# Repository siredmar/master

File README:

02.03.2014 - This is the repository for my masters thesis

-- Armin Schlegel

GIT instructions:
* adding new files
git add *

* deleting files from repo
git rm *

* commit changed files:
git commit -am 'message'

* push commit to github
git push origin master

* update local repo from github
git pull

--- 
creating a patch:
diff -uNr  original/ new/ > original.patch

use a patch:
cd original
patch -p1 < ../patch.file

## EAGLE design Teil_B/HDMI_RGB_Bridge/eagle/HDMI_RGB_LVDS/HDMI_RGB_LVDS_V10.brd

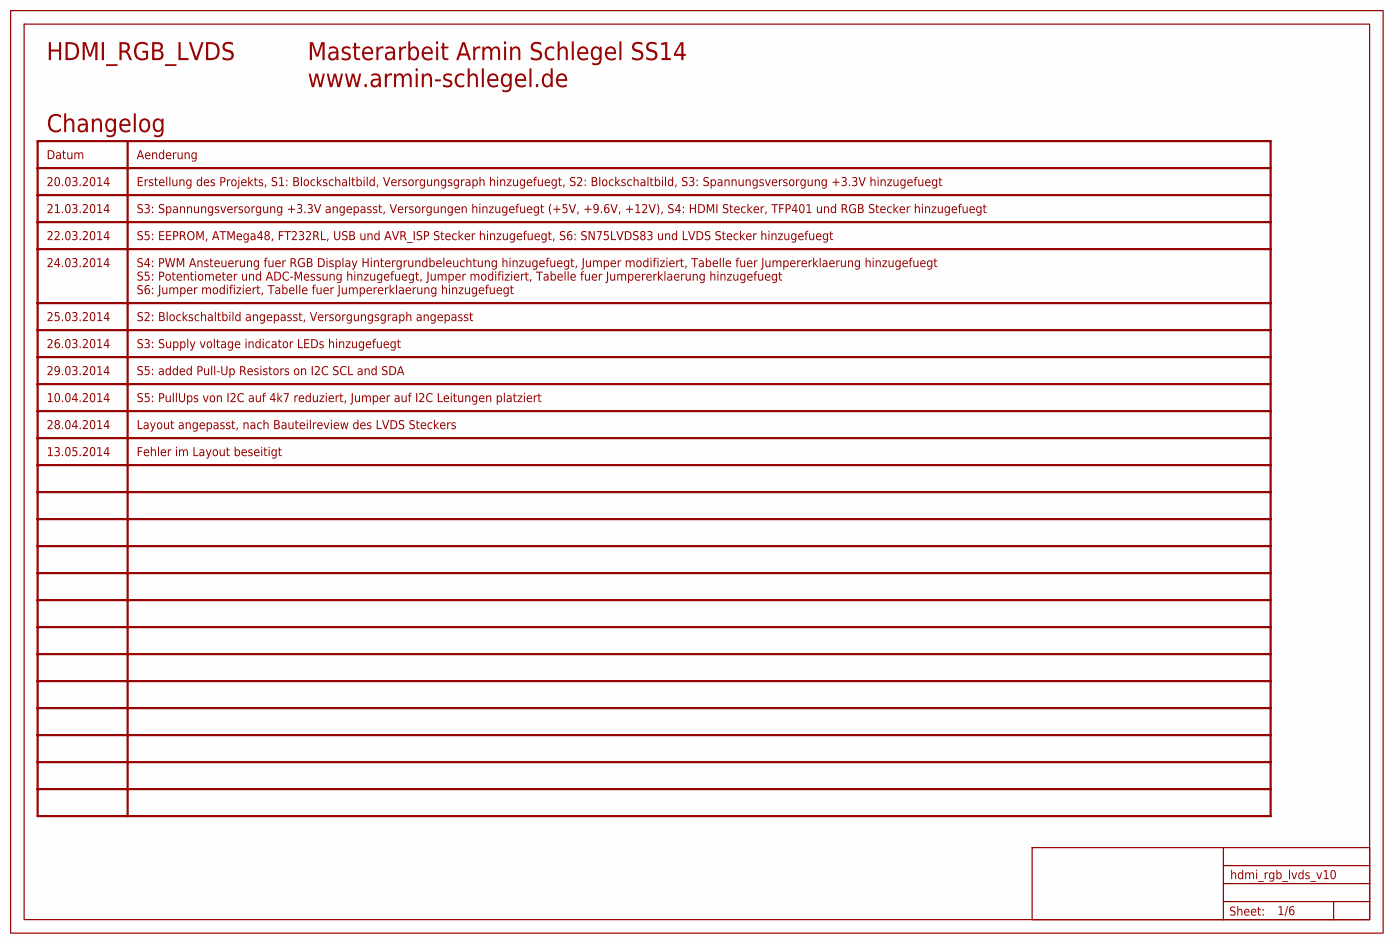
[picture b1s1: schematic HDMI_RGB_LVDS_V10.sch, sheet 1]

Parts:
U$1: FRAME_A3_LANDSCAPE; FRAME

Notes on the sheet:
Erstellung des Projekts, S1: Blockschaltbild, Versorgungsgraph hinzugefuegt, S2: Blockschaltbild, S3: Spannungsversorgung +3.3V hinzugefuegt
HDMI_RGB_LVDS
Masterarbeit Armin Schlegel SS14
www.armin-schlegel.de
Changelog
20.03.2014
Datum
Aenderung
21.03.2014
S3: Spannungsversorgung +3.3V angepasst, Versorgungen hinzugefuegt (+5V, +9.6V, +12V), S4: HDMI Stecker, TFP401 und RGB Stecker hinzugefuegt
22.03.2014
S5: EEPROM, ATMega48, FT232RL, USB und AVR_ISP Stecker hinzugefuegt, S6: SN75LVDS83 und LVDS Stecker hinzugefuegt
24.03.2014
S4: PWM Ansteuerung fuer RGB Display Hintergrundbeleuchtung hinzugefuegt, Jumper modifiziert, Tabelle fuer Jumpererklaerung hinzugefuegt S5: Potentiometer und ADC-Messung hinzugefuegt, Jumper modifiziert, Tabelle fuer Jumpererklaerung hinzugefuegt S6: Jumper modifiziert, Tabelle fuer Jumpererklaeru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
25.03.2014
S2: Blockschaltbild angepasst, Versorgungsgraph angepasst
26.03.2014
S3: Supply voltage indicator LEDs hinzugefuegt
29.03.2014
S5: added Pull-Up Resistors on I2C SCL and SDA
10.04.2014
S5: PullUps von I2C auf 4k7 reduziert, Jumper auf I2C Leitungen platziert
28.04.2014
Layout angepasst, nach Bauteilreview des LVDS Steckers
13.05.2014
Fehler im Layout beseitigt

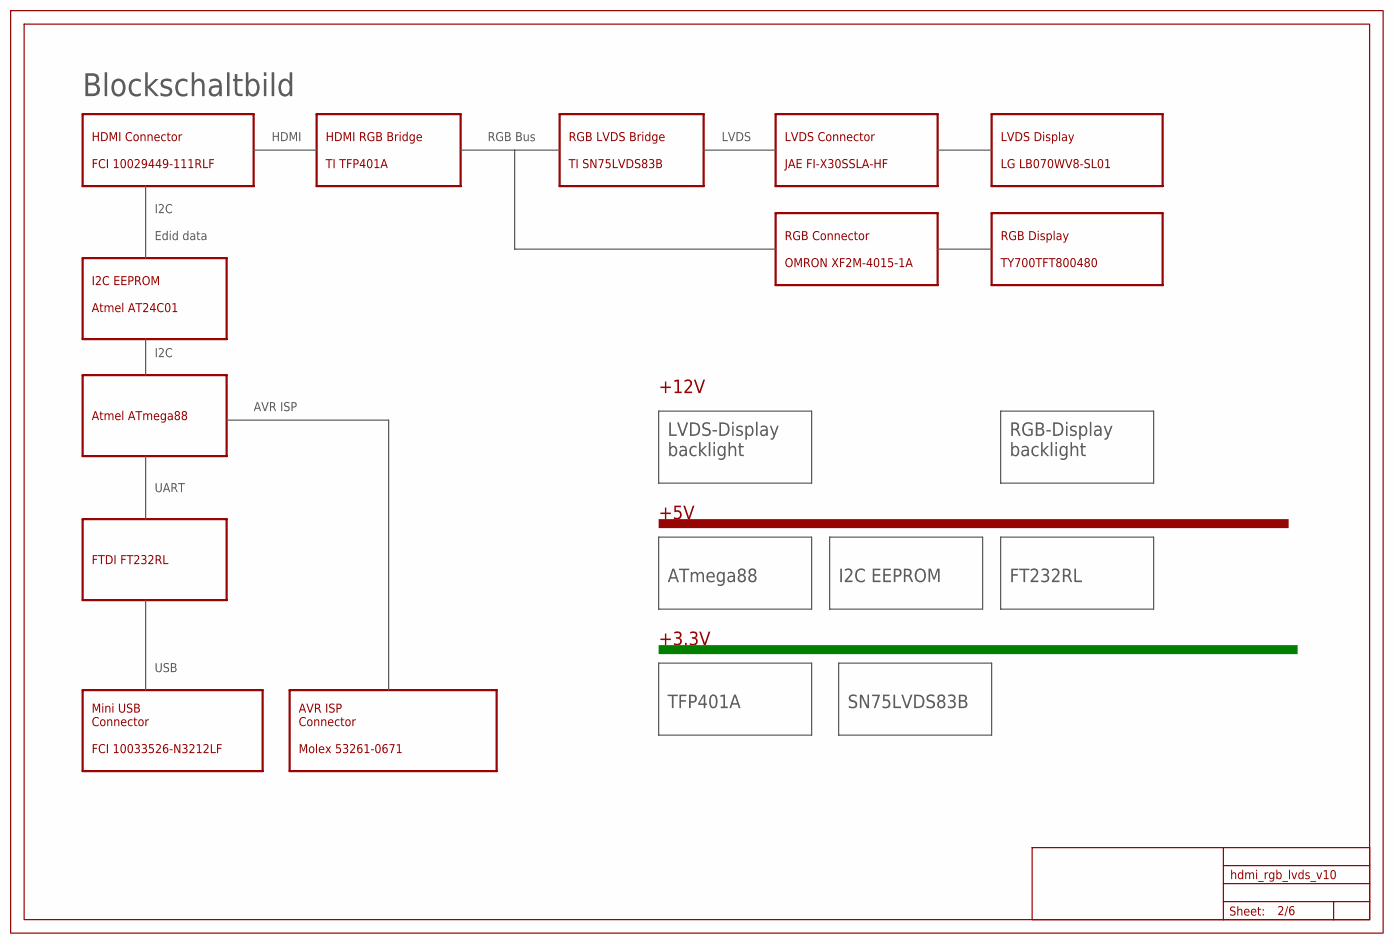
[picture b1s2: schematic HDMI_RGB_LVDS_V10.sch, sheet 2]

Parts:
U$15: FRAME_A3_LANDSCAPE; FRAME

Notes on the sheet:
HDMI Connector FCI 10029449-111RLF
LVDS Display LG LB070WV8-SL01
RGB Display TY700TFT800480
Mini USB Connector FCI 10033526-N3212LF
AVR ISP Connector Molex 53261-0671
LVDS Connector JAE FI-X30SSLA-HF
RGB Connector OMRON XF2M-4015-1A
HDMI RGB Bridge TI TFP401A
RGB LVDS Bridge TI SN75LVDS83B
I2C EEPROM Atmel AT24C01
Atmel ATmega88
Edid data
RGB Bus
LVDS
I2C
USB
AVR ISP
HDMI
Blockschaltbild
+3.3V
+12V
+5V
ATmega88
I2C EEPROM
FT232RL
TFP401A
LVDS-Display backlight
FTDI FT232RL
UART
RGB-Display backlight
SN75LVDS83B

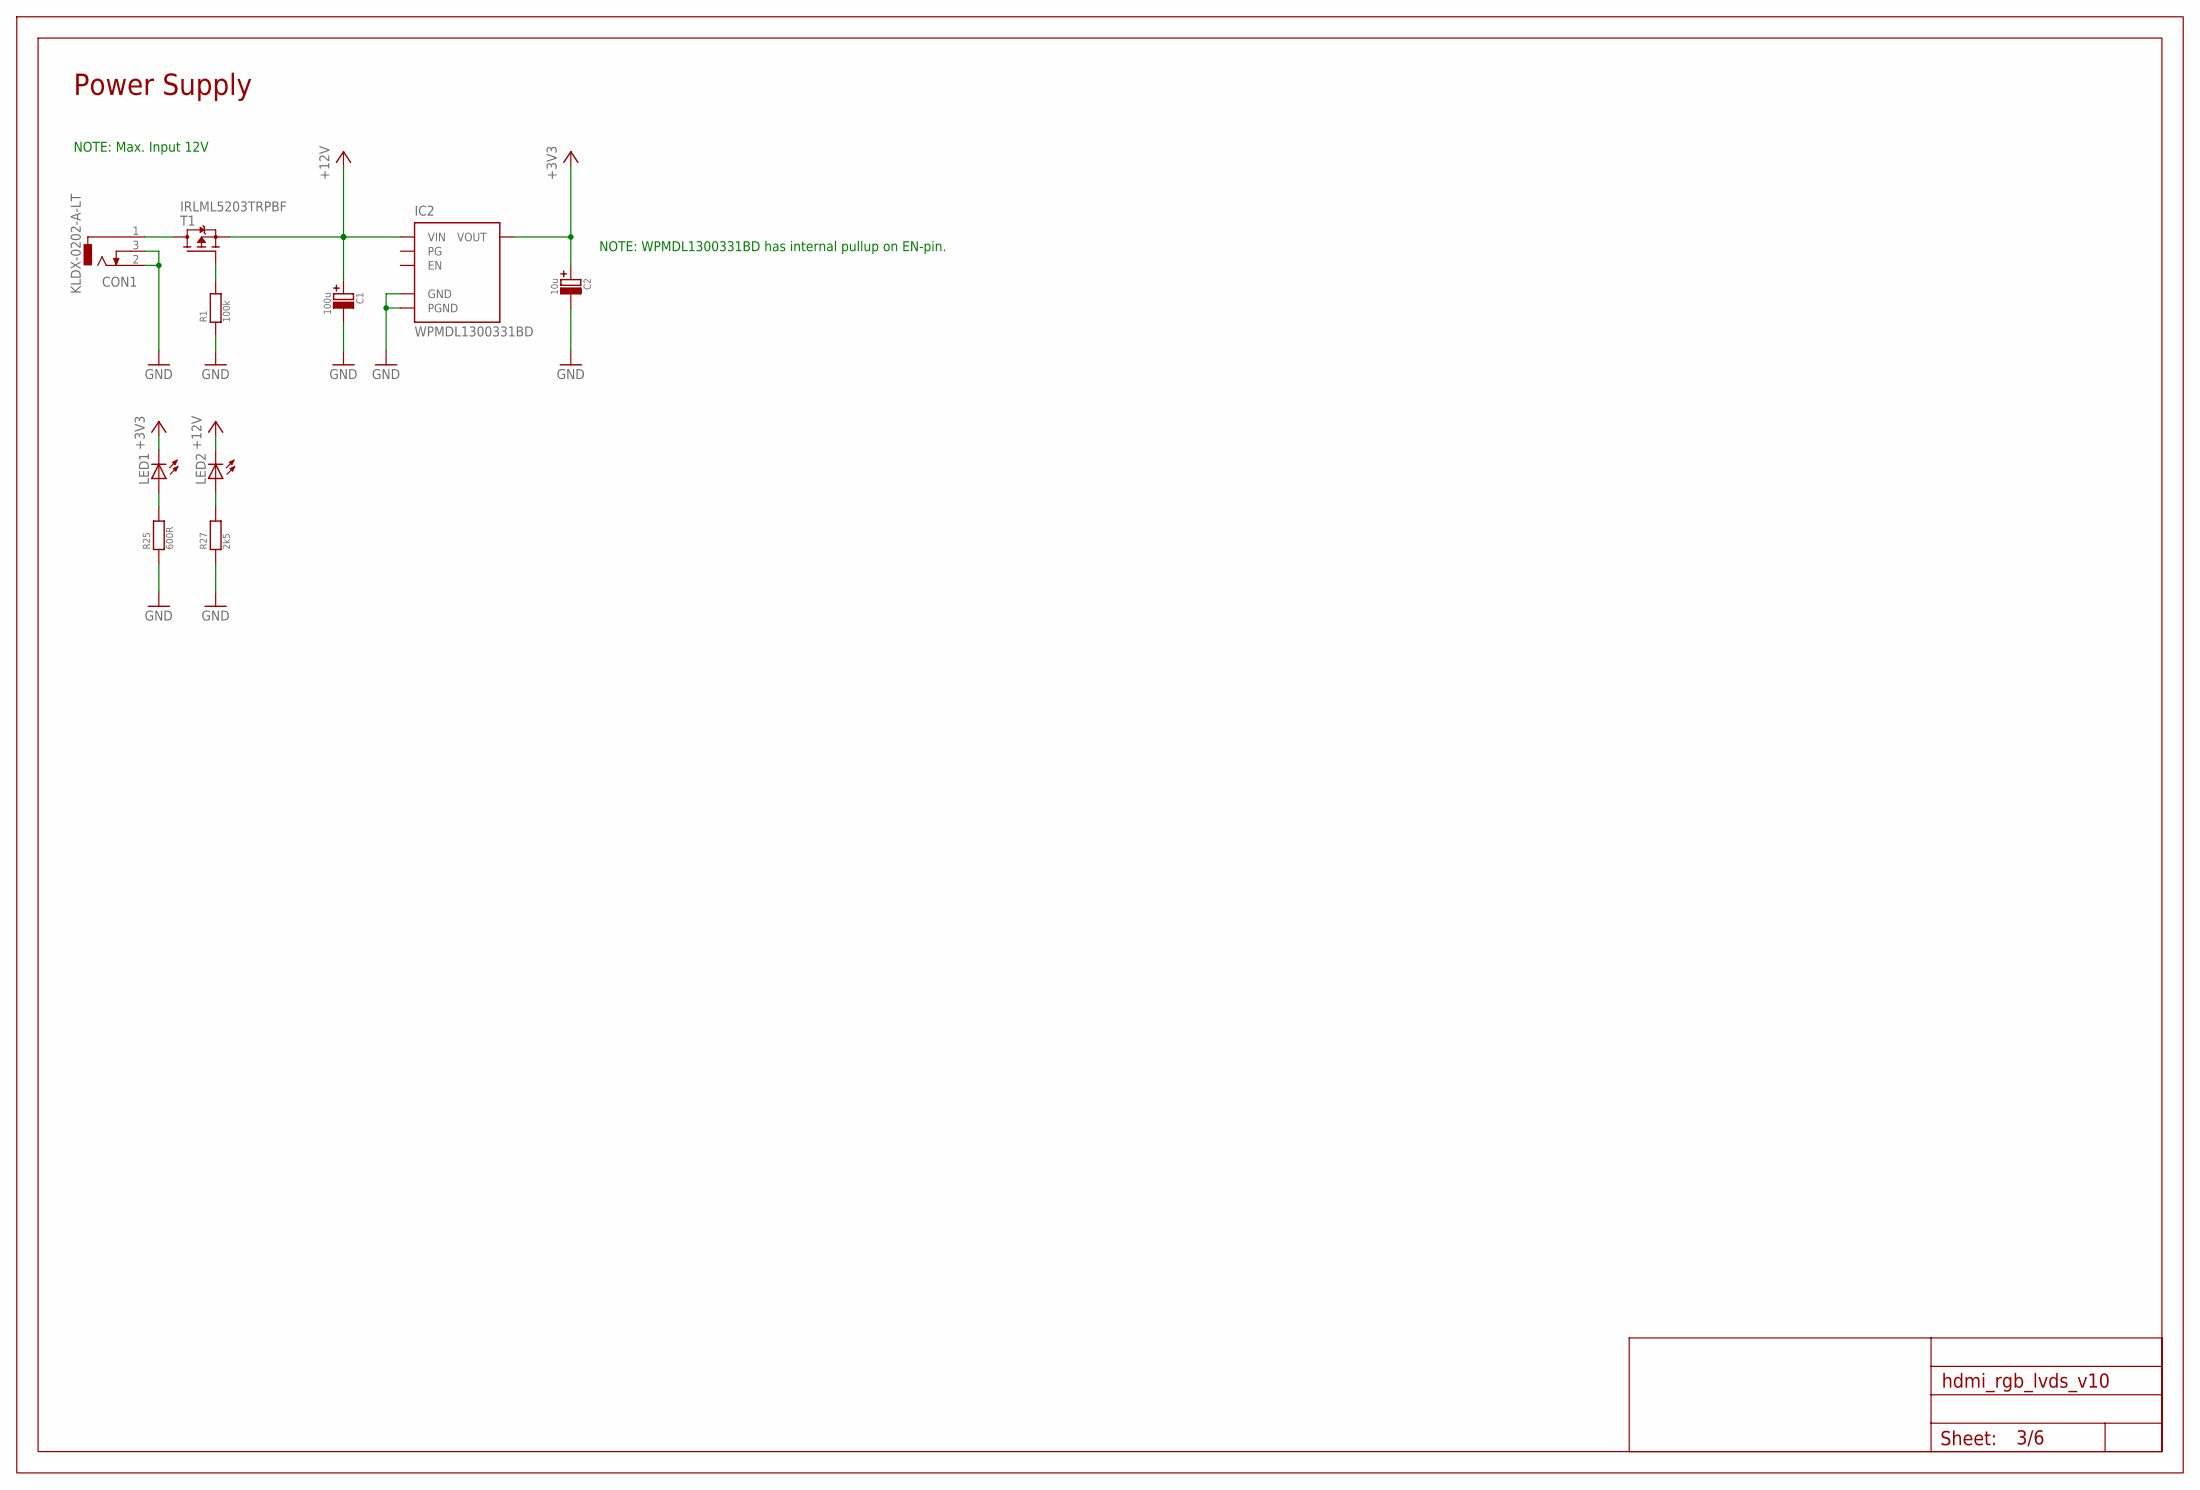
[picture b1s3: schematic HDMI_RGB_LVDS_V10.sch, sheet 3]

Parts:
C1: 100u; C_POL_6X6MM
C2: 10u; C_POL_4X4MM
CON1: KLDX-0202-A-LT
IC2: WPMDL1300331BD; TO263-5
LED1, LED2: LED0402
R1: 100k; R0402
R25: 600R; R0402
R27: 2k5; R0402
T1: IRLML5203TRPBF; SOT23
U$2: FRAME_A3_LANDSCAPE; FRAME

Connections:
+3V3: C2.+, IC2.3 (VOUT), LED1.C; also elsewhere on the board
+12V: C1.+, IC2.1 (VIN), LED2.C, T1.2 (S); also elsewhere on the board
GND: C1.-, C2.-, CON1.2 (3), CON1.3 (2), IC2.2 (GND), IC2.6 (PGND), R1.1, R25.1, R27.1; also elsewhere on the board
unnamed: CON1.1, T1.3 (D)
unnamed: R1.2, T1.1 (G)
unnamed: LED1.A, R25.2
unnamed: LED2.A, R27.2

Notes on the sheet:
Power Supply
NOTE: WPMDL1300331BD has internal pullup on EN-pin.
NOTE: Max. Input 12V

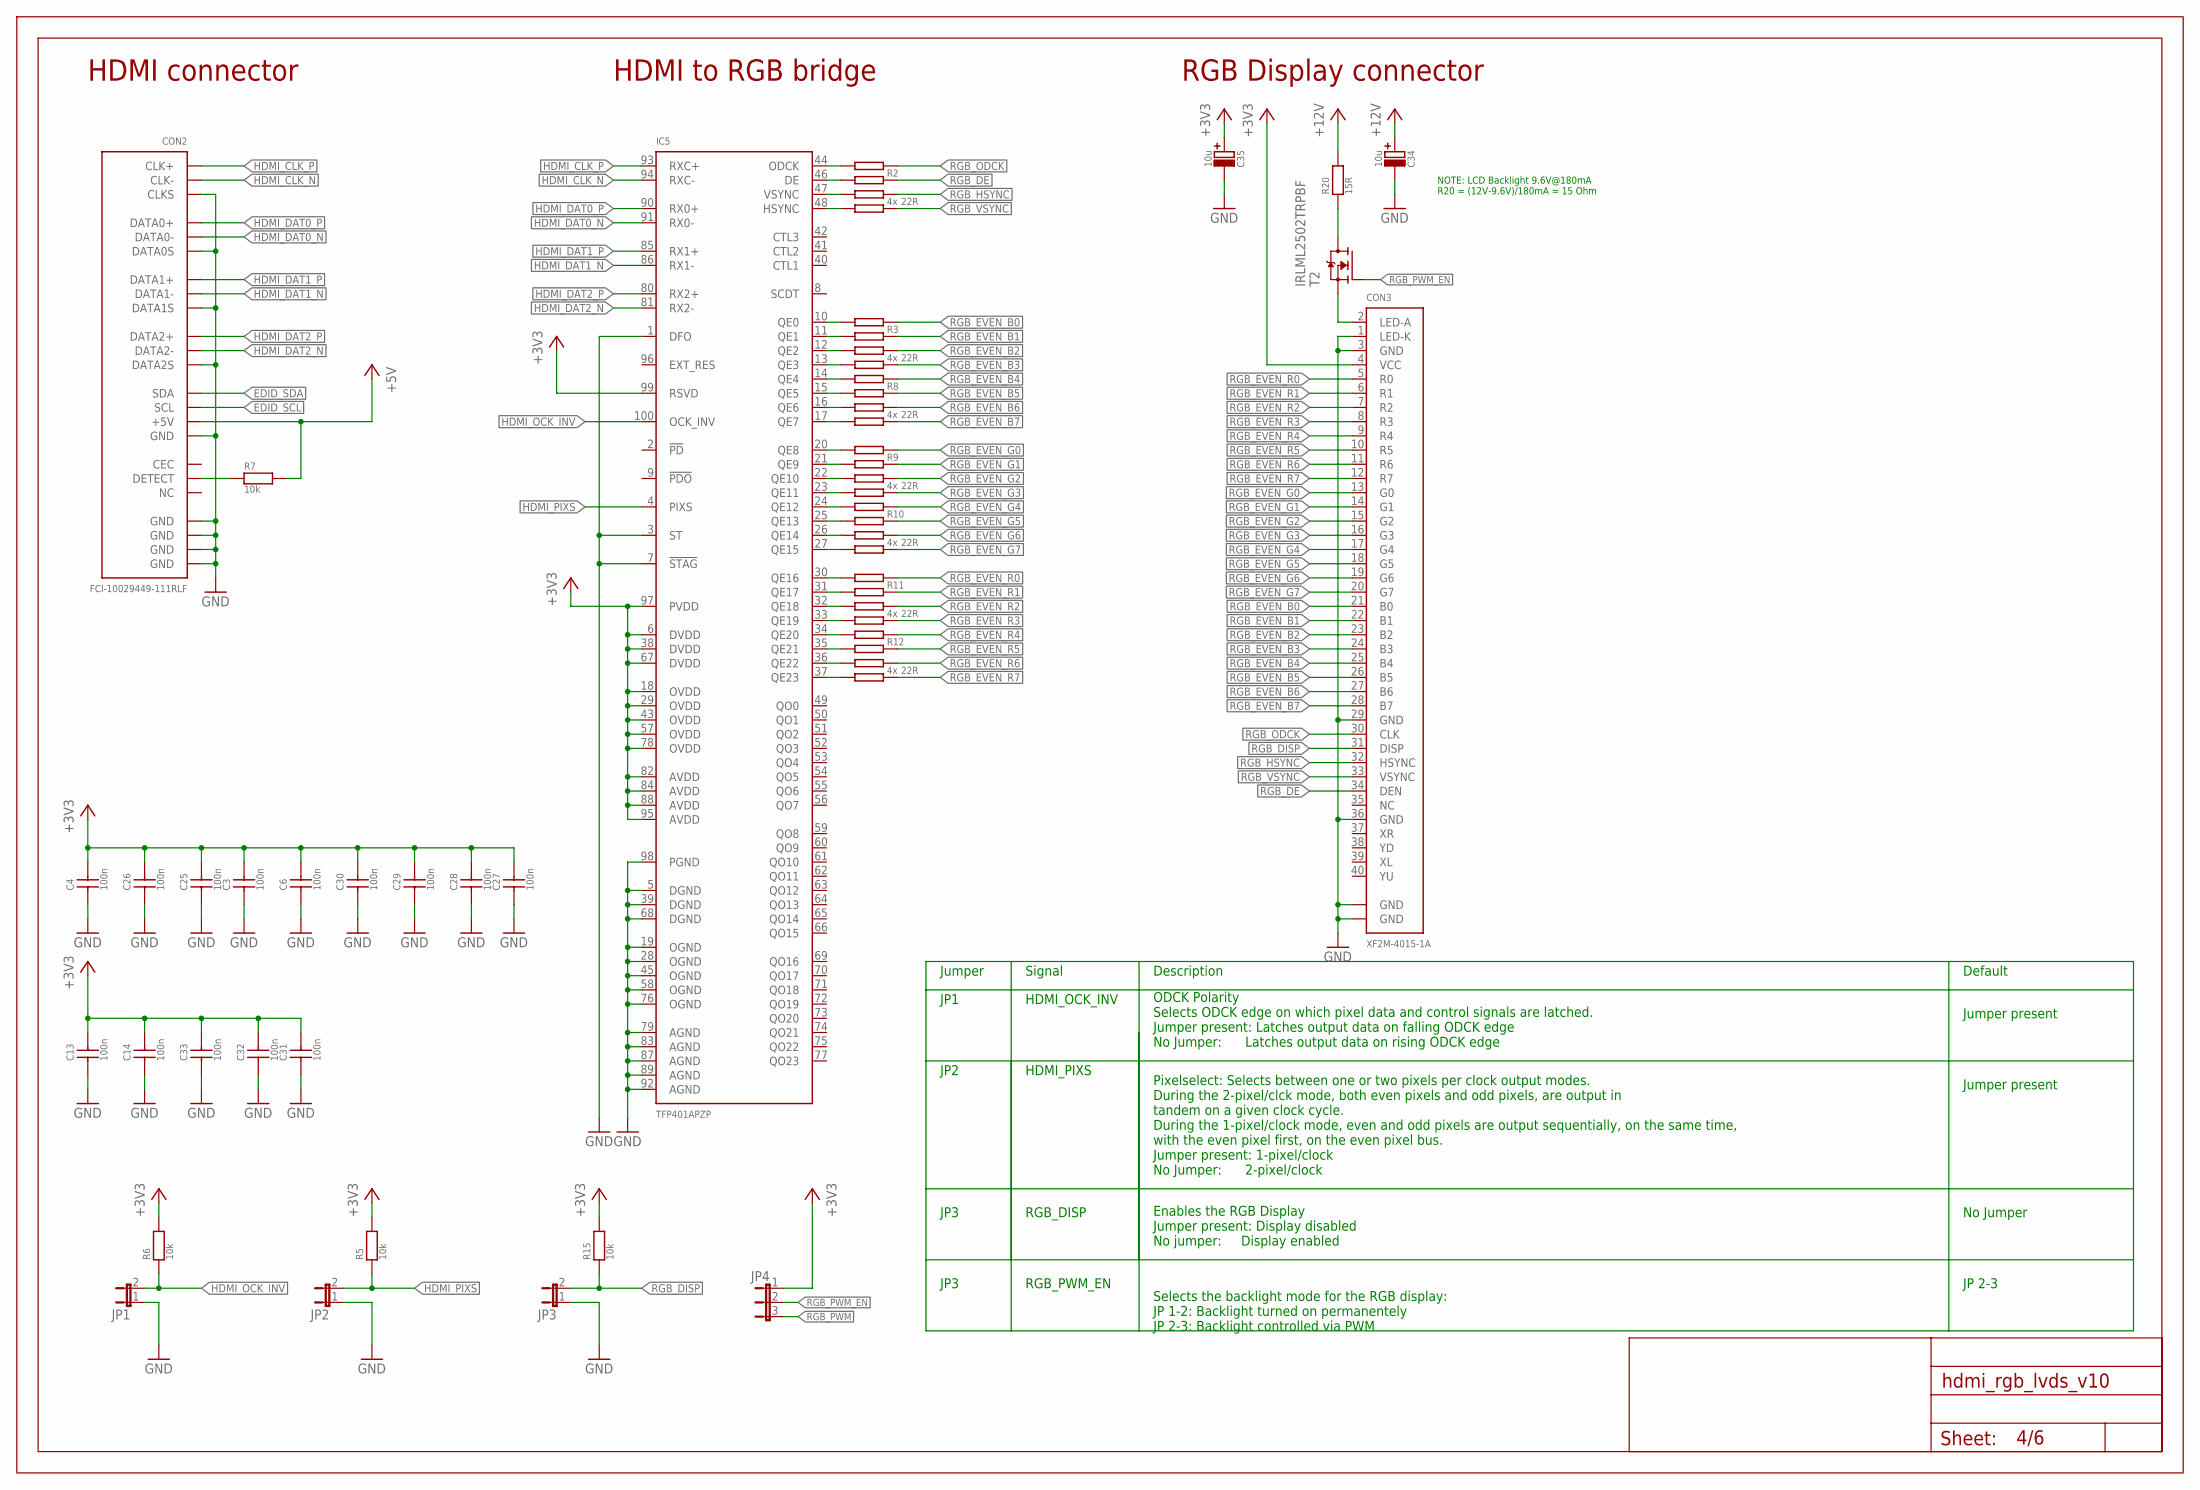
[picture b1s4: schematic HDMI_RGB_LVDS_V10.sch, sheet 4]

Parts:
C3, C4, C6, C13, C14, C25, C26, C27, C28, C29, C30, C31, C32, C33: 100n; C0402
C34, C35: 10u; C_POL_4X4MM
CON2: FCI-10029449-111RLF
CON3: XF2M-4015-1A
IC5: TFP401APZP; HTQFP-100
JP1, JP2, JP3: JUMPER2; JUMPER2_THROUGHHOLE
JP4: JUMPER3; JUMPER3_THROUGHHOLE
R2, R3, R8, R9, R10, R11, R12: 22R; R-ARRAY-4X0603
R5, R6, R7, R15: 10k; R0402
R20: 15R; R2512
T2: IRLML2502TRPBF; SOT23
U$3: FRAME_A3_LANDSCAPE; FRAME

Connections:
+3V3: C3.2, C4.2, C6.2, C13.2, C14.2, C25.2, C26.2, C27.2, C28.2, C29.2, C30.2, C31.2, C32.2, C33.2, C35.+, CON3.4 (VCC), IC5.6 (DVDD), IC5.18 (OVDD), IC5.29 (OVDD), IC5.38 (DVDD), IC5.43 (OVDD), IC5.57 (OVDD), IC5.67 (DVDD), IC5.78 (OVDD), IC5.82 (AVDD), IC5.84 (AVDD), IC5.88 (AVDD), IC5.95 (AVDD), IC5.97 (PVDD), IC5.99 (RSVD), JP4.1, R5.2, R6.2, R15.2; also elsewhere on the board
+5V: CON2.18 (+5V), R7.2; also elsewhere on the board
+12V: C34.+, R20.2; also elsewhere on the board
EDID_SCL: CON2.15 (SCL); also elsewhere on the board
EDID_SDA: CON2.16 (SDA); also elsewhere on the board
GND: C3.1, C4.1, C6.1, C13.1, C14.1, C25.1, C26.1, C27.1, C28.1, C29.1, C30.1, C31.1, C32.1, C33.1, C34.-, C35.-, CON2.2 (DATA2S), CON2.5 (DATA1S), CON2.8 (DATA0S), CON2.11 (CLKS), CON2.17 (GND), CON2.GND@1 (GND), CON2.GND@2 (GND), CON2.GND@3 (GND), CON2.GND@4 (GND), CON3.1 (LED-K), CON3.3 (GND), CON3.29 (GND), CON3.36 (GND), CON3.GND@1 (GND), CON3.GND@2 (GND), IC5.1 (DFO), IC5.3 (ST), IC5.5 (DGND), IC5.7 (!STAG), IC5.19 (OGND), IC5.28 (OGND), IC5.39 (DGND), IC5.45 (OGND), IC5.58 (OGND), IC5.68 (DGND), IC5.76 (OGND), IC5.79 (AGND), IC5.83 (AGND), IC5.87 (AGND), IC5.89 (AGND), IC5.92 (AGND), IC5.98 (PGND), JP1.1, JP2.1, JP3.1; also elsewhere on the board
HDMI_CLK_N: CON2.12 (CLK-), IC5.94 (RXC-)
HDMI_CLK_P: CON2.10 (CLK+), IC5.93 (RXC+)
HDMI_DAT0_N: CON2.9 (DATA0-), IC5.91 (RX0-)
HDMI_DAT0_P: CON2.7 (DATA0+), IC5.90 (RX0+)
HDMI_DAT1_N: CON2.6 (DATA1-), IC5.86 (RX1-)
HDMI_DAT1_P: CON2.4 (DATA1+), IC5.85 (RX1+)
HDMI_DAT2_N: CON2.3 (DATA2-), IC5.81 (RX2-)
HDMI_DAT2_P: CON2.1 (DATA2+), IC5.80 (RX2+)
HDMI_OCK_INV: IC5.100 (OCK_INV), JP1.2, R6.1
HDMI_PIXS: IC5.4 (PIXS), JP2.2, R5.1
INT_RGB_DE: IC5.46 (DE), R2.3M
INT_RGB_EVEN_B0: IC5.10 (QE0), R3.4M
INT_RGB_EVEN_B1: IC5.11 (QE1), R3.3M
INT_RGB_EVEN_B2: IC5.12 (QE2), R3.2M
INT_RGB_EVEN_B3: IC5.13 (QE3), R3.1M
INT_RGB_EVEN_B4: IC5.14 (QE4), R8.4M
INT_RGB_EVEN_B5: IC5.15 (QE5), R8.3M
INT_RGB_EVEN_B6: IC5.16 (QE6), R8.2M
INT_RGB_EVEN_B7: IC5.17 (QE7), R8.1M
INT_RGB_EVEN_G0: IC5.20 (QE8), R9.4M
INT_RGB_EVEN_G1: IC5.21 (QE9), R9.3M
INT_RGB_EVEN_G2: IC5.22 (QE10), R9.2M
INT_RGB_EVEN_G3: IC5.23 (QE11), R9.1M
INT_RGB_EVEN_G4: IC5.24 (QE12), R10.4M
INT_RGB_EVEN_G5: IC5.25 (QE13), R10.3M
INT_RGB_EVEN_G6: IC5.26 (QE14), R10.2M
INT_RGB_EVEN_G7: IC5.27 (QE15), R10.1M
INT_RGB_EVEN_R0: IC5.30 (QE16), R11.4M
INT_RGB_EVEN_R1: IC5.31 (QE17), R11.3M
INT_RGB_EVEN_R2: IC5.32 (QE18), R11.2M
INT_RGB_EVEN_R3: IC5.33 (QE19), R11.1M
INT_RGB_EVEN_R4: IC5.34 (QE20), R12.4M
INT_RGB_EVEN_R5: IC5.35 (QE21), R12.3M
INT_RGB_EVEN_R6: IC5.36 (QE22), R12.2M
INT_RGB_EVEN_R7: IC5.37 (QE23), R12.1M
INT_RGB_HSYNC: IC5.47 (VSYNC), R2.2M
INT_RGB_ODCK: IC5.44 (ODCK), R2.4M
INT_RGB_VSYNC: IC5.48 (HSYNC), R2.1M
unnamed: CON2.19 (DETECT), R7.1
unnamed: CON3.2 (LED-A), T2.2 (S)
unnamed: R20.1, T2.3 (D)
RGB_DE: CON3.34 (DEN), R2.3P; also elsewhere on the board
RGB_DISP: CON3.31 (DISP), JP3.2, R15.1
RGB_EVEN_B0: CON3.21 (B0), R3.4P; also elsewhere on the board
RGB_EVEN_B1: CON3.22 (B1), R3.3P; also elsewhere on the board
RGB_EVEN_B2: CON3.23 (B2), R3.2P; also elsewhere on the board
RGB_EVEN_B3: CON3.24 (B3), R3.1P; also elsewhere on the board
RGB_EVEN_B4: CON3.25 (B4), R8.4P; also elsewhere on the board
RGB_EVEN_B5: CON3.26 (B5), R8.3P; also elsewhere on the board
RGB_EVEN_B6: CON3.27 (B6), R8.2P; also elsewhere on the board
RGB_EVEN_B7: CON3.28 (B7), R8.1P; also elsewhere on the board
RGB_EVEN_G0: CON3.13 (G0), R9.4P; also elsewhere on the board
RGB_EVEN_G1: CON3.14 (G1), R9.3P; also elsewhere on the board
RGB_EVEN_G2: CON3.15 (G2), R9.2P; also elsewhere on the board
RGB_EVEN_G3: CON3.16 (G3), R9.1P; also elsewhere on the board
RGB_EVEN_G4: CON3.17 (G4), R10.4P; also elsewhere on the board
RGB_EVEN_G5: CON3.18 (G5), R10.3P; also elsewhere on the board
RGB_EVEN_G6: CON3.19 (G6), R10.2P; also elsewhere on the board
RGB_EVEN_G7: CON3.20 (G7), R10.1P; also elsewhere on the board
RGB_EVEN_R0: CON3.5 (R0), R11.4P; also elsewhere on the board
RGB_EVEN_R1: CON3.6 (R1), R11.3P; also elsewhere on the board
RGB_EVEN_R2: CON3.7 (R2), R11.2P; also elsewhere on the board
RGB_EVEN_R3: CON3.8 (R3), R11.1P; also elsewhere on the board
RGB_EVEN_R4: CON3.9 (R4), R12.4P; also elsewhere on the board
RGB_EVEN_R5: CON3.10 (R5), R12.3P; also elsewhere on the board
RGB_EVEN_R6: CON3.11 (R6), R12.2P; also elsewhere on the board
RGB_EVEN_R7: CON3.12 (R7), R12.1P; also elsewhere on the board
RGB_HSYNC: CON3.32 (HSYNC), R2.2P; also elsewhere on the board
RGB_ODCK: CON3.30 (CLK), R2.4P
RGB_PWM: JP4.3; also elsewhere on the board
RGB_PWM_EN: JP4.2, T2.1 (G)
RGB_VSYNC: CON3.33 (VSYNC), R2.1P; also elsewhere on the board

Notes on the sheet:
HDMI connector
NOTE: LCD Backlight 9.6V@180mA R20 = (12V-9.6V)/180mA = 15 Ohm
JP1
JP2
JP3
Jumper
Description
Enables the RGB Display Jumper present: Display disabled No jumper: Display enabled
Signal
RGB_DISP
HDMI_PIXS
HDMI_OCK_INV
ODCK Polarity Selects ODCK edge on which pixel data and control signals are latched. Jumper present: Latches output data on falling ODCK edge No Jumper: Latches output data on rising ODCK edge
Pixelselect: Selects between one or two pixels per clock output modes. During the 2-pixel/clck mode, both even pixels and odd pixels, are output in tandem on a given clock cycle. During the 1-pixel/clock mode, even and odd pixels are output sequentially, on the same time, with the even pixel first,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
RGB_PWM_EN
Selects the backlight mode for the RGB display: JP 1-2: Backlight turned on permanentely JP 2-3: Backlight controlled via PWM
Default
No Jumper
JP 2-3
Jumper present
HDMI to RGB bridge
RGB Display connector

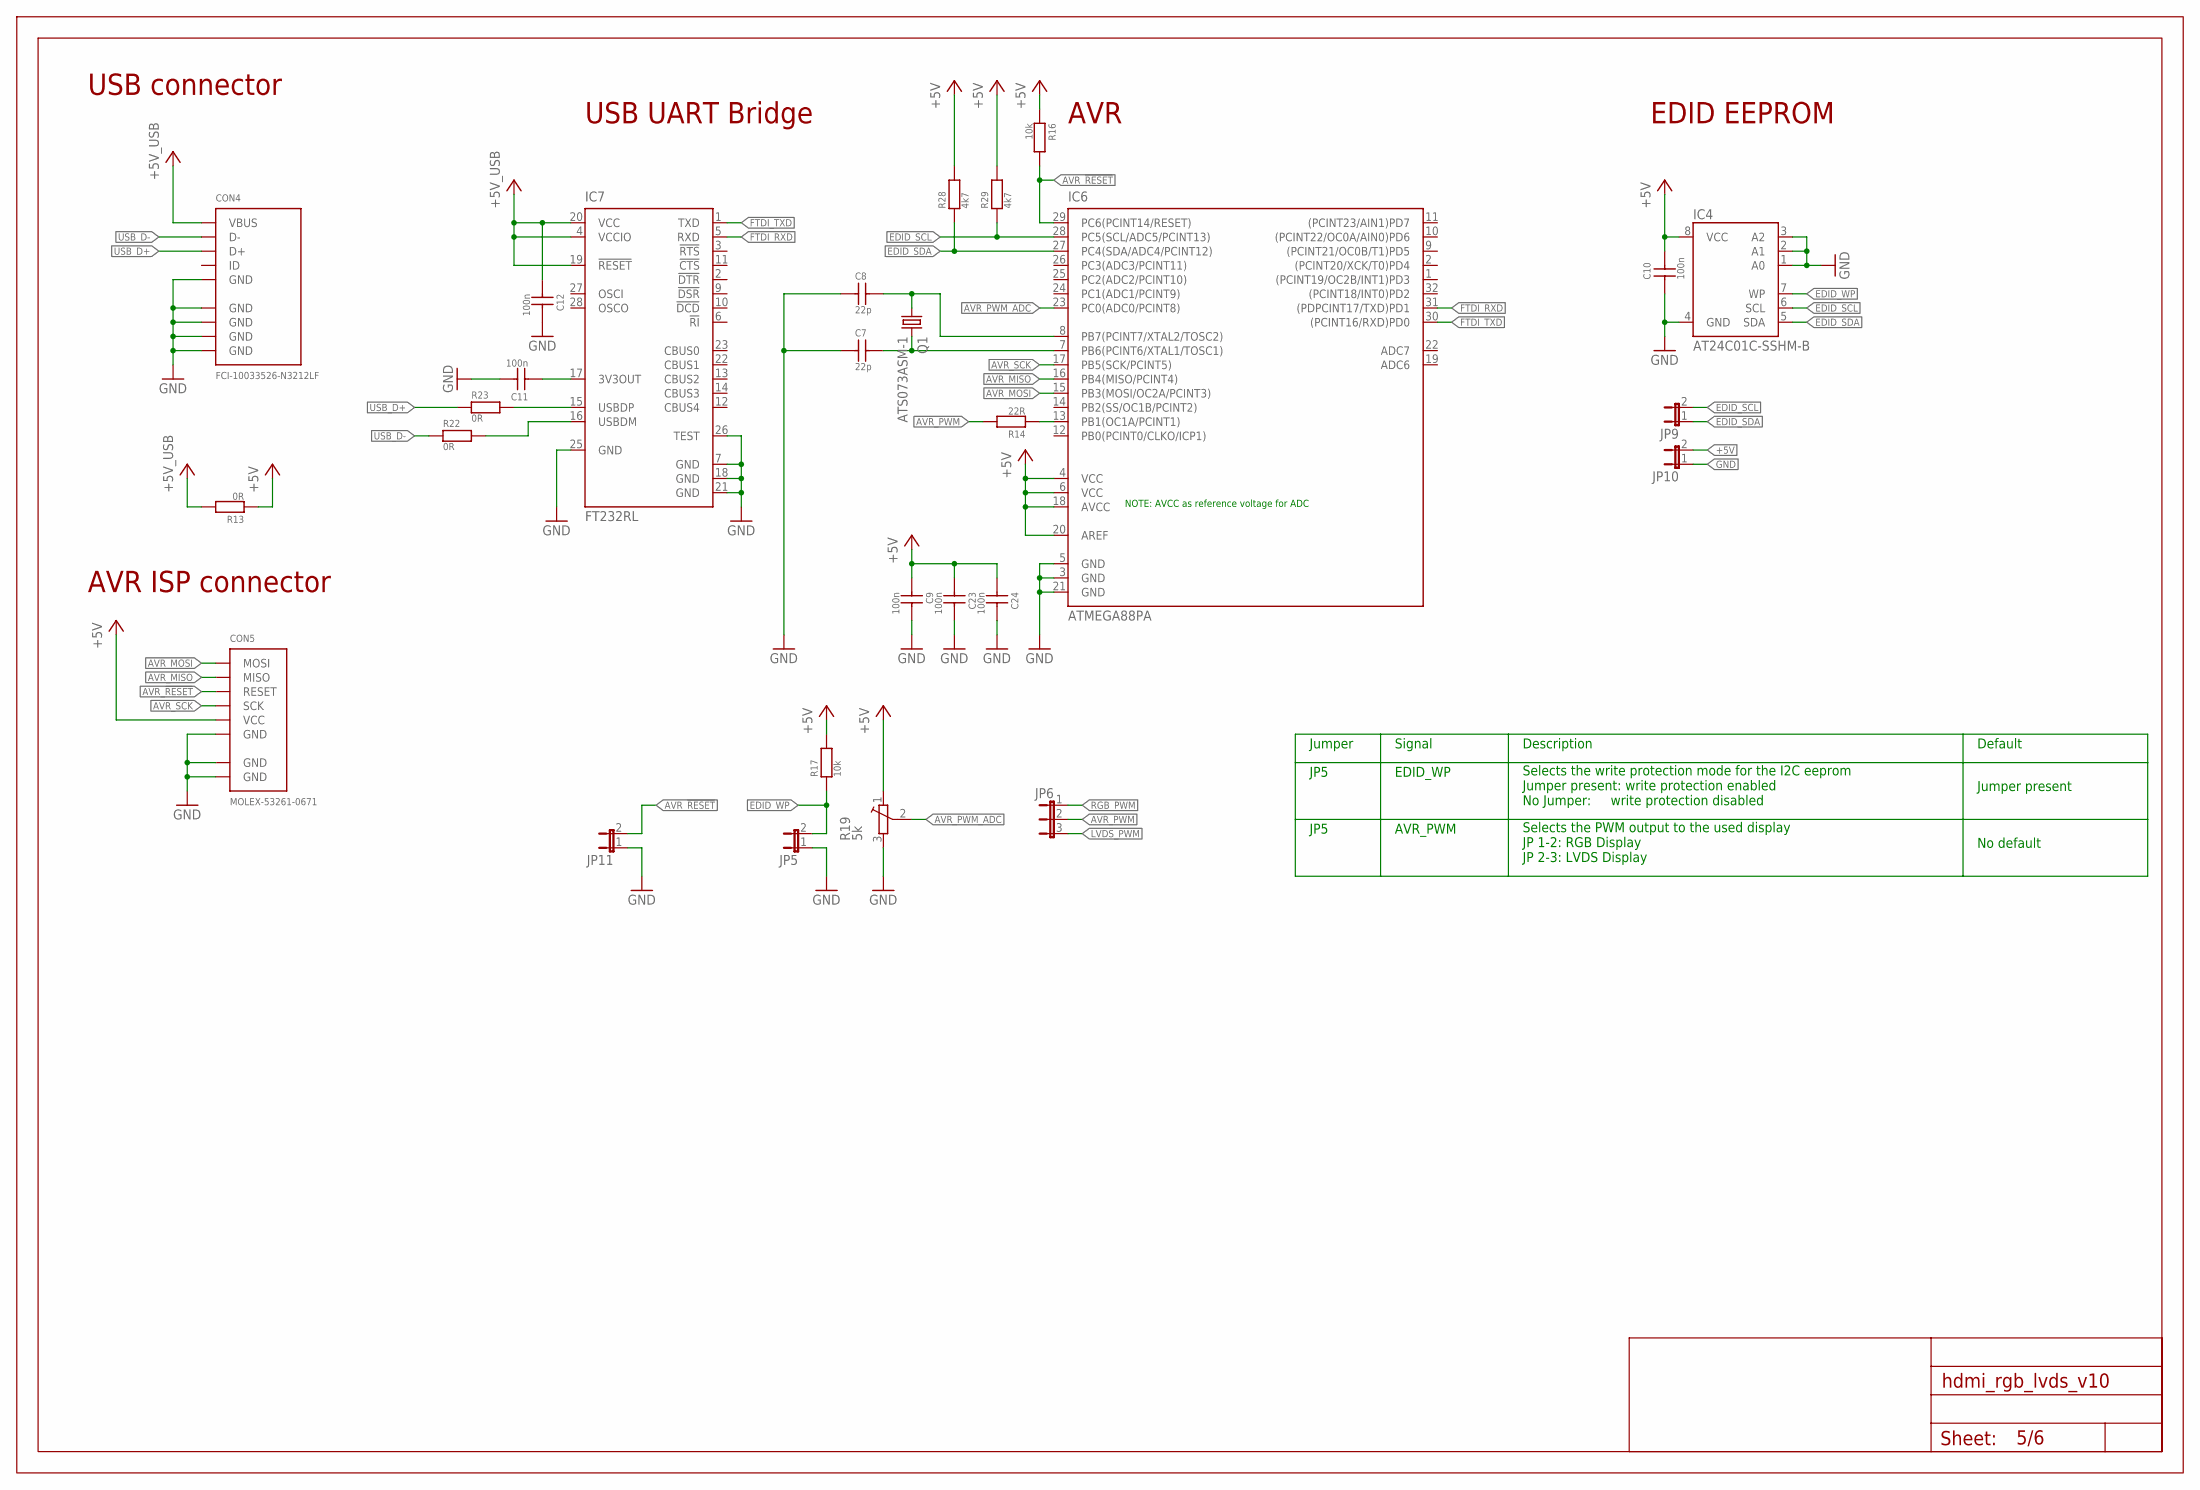
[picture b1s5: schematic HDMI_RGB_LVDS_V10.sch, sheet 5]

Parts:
C7, C8: 22p; C0402
C9, C10, C11, C12, C23, C24: 100n; C0402
CON4: FCI-10033526-N3212LF
CON5: MOLEX-53261-0671
IC4: AT24C01C-SSHM-B; SOIC8
IC6: ATMEGA88PA; TQFP32
IC7: FT232RL; SSOP28
JP5, JP9, JP10, JP11: JUMPER2; JUMPER2_THROUGHHOLE
JP6: JUMPER3; JUMPER3_THROUGHHOLE
Q1: ATS073ASM-1; HC49/USSM
R13, R22, R23: 0R; R0402
R14: 22R; R0402
R16, R17: 10k; R0402
R19: 5k; 35WR5KLFTR
R28, R29: 4k7; R0402
U$4: FRAME_A3_LANDSCAPE; FRAME

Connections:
+5V: C9.1, C10.2, C23.1, C24.1, CON5.5 (VCC), IC4.8 (VCC), IC6.4 (VCC), IC6.6 (VCC), IC6.18 (AVCC), IC6.20 (AREF), JP10.2, R13.1, R16.1, R17.2, R19.1 (E), R28.2, R29.2; also elsewhere on the board
+5V_USB: C12.1, CON4.1 (VBUS), IC7.4 (VCCIO), IC7.19 (!RESET), IC7.20 (VCC), R13.2
AVR_!RESET: CON5.3 (RESET), IC6.29 (PC6(PCINT14/RESET)), JP11.2, R16.2
AVR_MISO: CON5.2 (MISO), IC6.16 (PB4(MISO/PCINT4))
AVR_MOSI: CON5.1 (MOSI), IC6.15 (PB3(MOSI/OC2A/PCINT3))
AVR_PWM: JP6.2, R14.2
AVR_PWM_ADC: IC6.23 (PC0(ADC0/PCINT8)), R19.2 (S)
AVR_SCK: CON5.4 (SCK), IC6.17 (PB5(SCK/PCINT5))
AVR_XTAL1: C7.2, IC6.7 (PB6(PCINT6/XTAL1/TOSC1)), Q1.2
AVR_XTAL2: C8.2, IC6.8 (PB7(PCINT7/XTAL2/TOSC2)), Q1.1
EDID_SCL: IC4.6 (SCL), IC6.28 (PC5(SCL/ADC5/PCINT13)), JP9.2, R29.1; also elsewhere on the board
EDID_SDA: IC4.5 (SDA), IC6.27 (PC4(SDA/ADC4/PCINT12)), JP9.1, R28.1; also elsewhere on the board
EDID_WP: IC4.7 (WP), JP5.2, R17.1
FTDI_3V3OUT: C11.1, IC7.17 (3V3OUT)
FTDI_RXD: IC6.31 ((PDPCINT17/TXD)PD1), IC7.5 (RXD)
FTDI_TXD: IC6.30 ((PCINT16/RXD)PD0), IC7.1 (TXD)
GND: C7.1, C8.1, C9.2, C10.1, C11.2, C12.2, C23.2, C24.2, CON4.5 (GND), CON4.GND@1 (GND), CON4.GND@2 (GND), CON4.GND@3 (GND), CON4.GND@4 (GND), CON5.6 (GND), CON5.GND@1 (GND), CON5.GND@2 (GND), IC4.1 (A0), IC4.2 (A1), IC4.3 (A2), IC4.4 (GND), IC6.3 (GND), IC6.5 (GND), IC6.21 (GND), IC7.7 (GND), IC7.18 (GND), IC7.21 (GND), IC7.25 (GND), IC7.26 (TEST), JP5.1, JP10.1, JP11.1, R19.3 (A); also elsewhere on the board
LVDS_PWM: JP6.3; also elsewhere on the board
unnamed: IC6.13 (PB1(OC1A/PCINT1)), R14.1
RGB_PWM: JP6.1; also elsewhere on the board
USB_D+: CON4.3 (D+), R23.1
USB_D-: CON4.2 (D-), R22.1

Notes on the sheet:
NOTE: AVCC as reference voltage for ADC
JP5
Jumper
Description
Signal
EDID_WP
Selects the write protection mode for the I2C eeprom Jumper present: write protection enabled No Jumper: write protection disabled
Selects the PWM output to the used display JP 1-2: RGB Display JP 2-3: LVDS Display
AVR_PWM
Default
Jumper present
No default
EDID EEPROM
AVR
USB UART Bridge
AVR ISP connector
USB connector

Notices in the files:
parts and their libraries:
Wurth_Electronics_Midcom_Speedy_and_stan: Copyright: Wurth Electronics Midcom, Inc.
